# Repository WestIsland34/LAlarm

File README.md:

# 機体発見アラーム (LAlarm)

直径 φ10 mm・重さ 1 g の、超小型・軽量の機体発見アラームです。
1 分ごとに分報（5 分後なら 5 回「ピーッ」）が鳴り、7 分後からアラームが鳴り続けます。

**[説明ページ](https://westisland.jp/lalarm/)**

## 基板

| 表 | 裏 |
|---|---|
|  |  |

## フォルダ

- `LALARM/` … 基板 (KiCad)
- `LALARM.X/` … PIC10F202 のプログラム (MPLAB X / XC8)

## 接続

- K110S: B+ と B- に接続
- それ以外の機体: S.BUS のコネクタなどに接続

[にしやん工房](https://westisland.jp/)

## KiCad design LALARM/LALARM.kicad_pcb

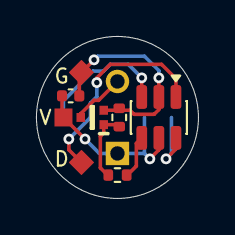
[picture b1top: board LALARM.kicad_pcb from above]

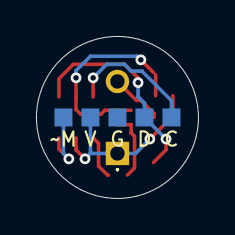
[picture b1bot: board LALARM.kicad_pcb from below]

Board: 2 copper layers, 9.0 x 9.0 mm, 13 parts (5 on the bottom side), 7 nets.

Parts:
BZ1: AT-0927-TT-5-R; AT0927TT5R
C: TestPoint_Pad_1.0x1.0mm
C1: 104; C_0402_1005Metric
D: TestPoint_Pad_1.0x1.0mm
D#2: TestPoint_Pad_1.0x1.0mm
G: TestPoint_Pad_1.0x1.0mm
G#2: TestPoint_Pad_1.0x1.0mm
Q1: RUM002N05T2L; SOTFL40P120X55-3N
R1: 1k; R_0402_1005Metric
R2: 10k; R_0402_1005Metric
U1: PIC10F202-IOT; SOT-23-6
V: TestPoint_Pad_1.0x1.0mm
V#2: TestPoint_Pad_1.0x1.0mm

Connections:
C: C.1, U1.3 (GP1)
D: D.1, D#2.1, U1.1 (GP0)
GND: C1.2, G.1, Q1.2 (S), R2.1, U1.2 (VSS)
unnamed: BZ1.2 (-), Q1.3 (D)
unnamed: Q1.1 (G), R1.1, R2.2
unnamed: R1.2, U1.4 (GP2)
VCC: BZ1.1 (+), C1.1, U1.5 (VDD), V.1, V#2.1
